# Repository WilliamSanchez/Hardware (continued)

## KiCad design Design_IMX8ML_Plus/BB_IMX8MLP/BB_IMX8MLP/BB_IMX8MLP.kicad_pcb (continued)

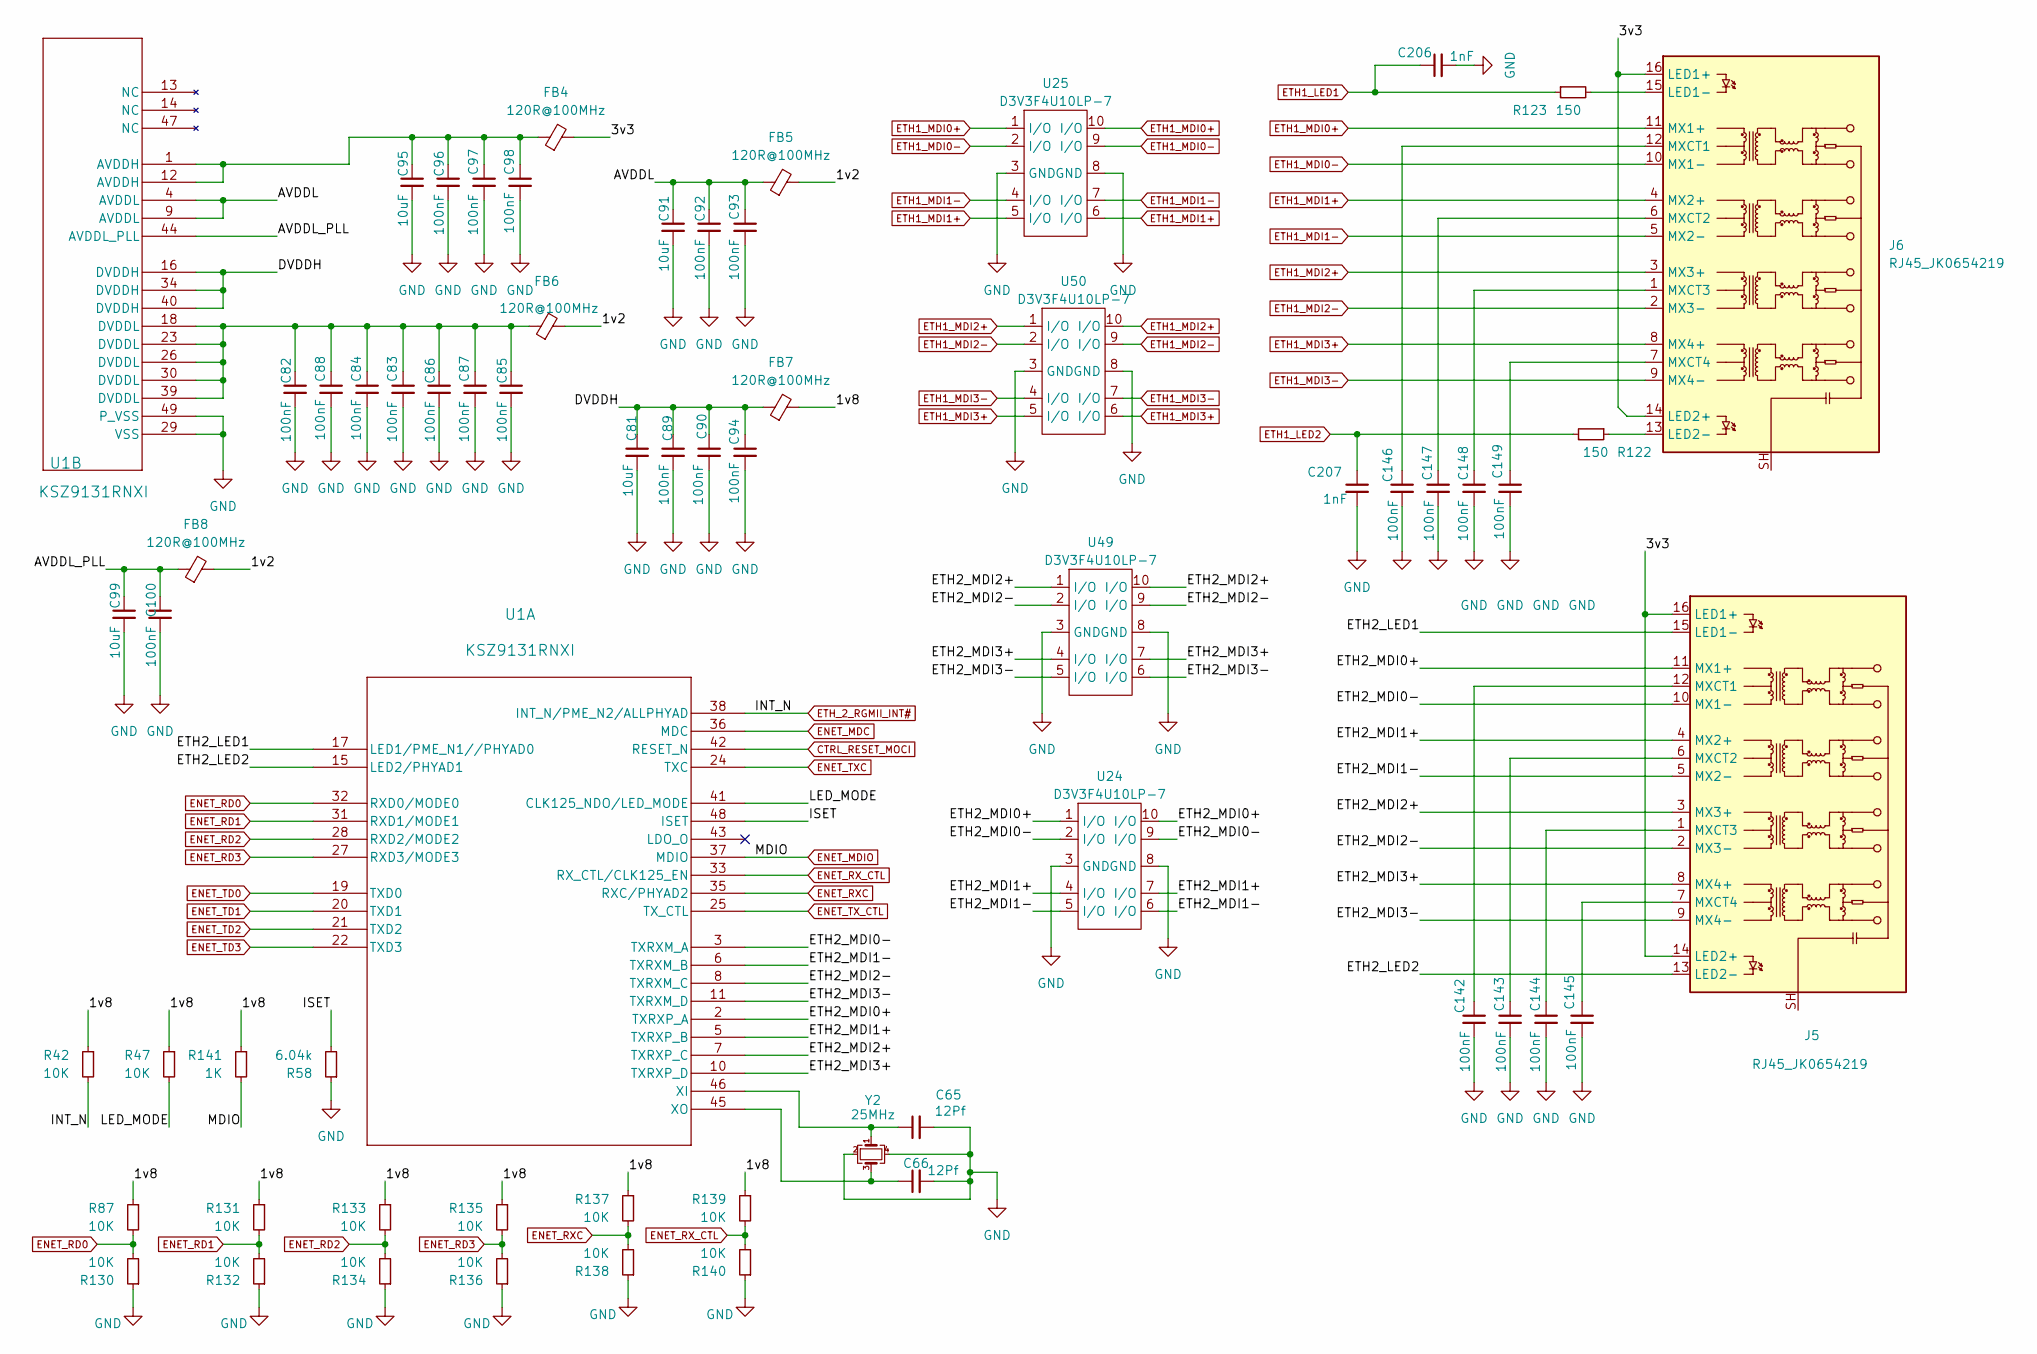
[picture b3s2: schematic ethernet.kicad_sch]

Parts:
C65, C66: 12Pf; C_0402_1005Metric
C81, C91, C95, C99: 10uF; C_0402_1005Metric
C82, C83, C84, C85, C86, C87, C88, C89, C90, C92, C93, C94, C96, C97, C98, C100, C142, C143, C144, C145, C146, C147, C148, C149: 100nF; C_0402_1005Metric
C206, C207: 1nF; C_0402_1005Metric
FB4, FB5, FB6, FB7, FB8: 120R@100MHz; L_0603_1608Metric
J5, J6: RJ45_JK0654219; BEL_A829-1J1T-KM
R42, R47: 10K; R_0402_1005Metric
R58: 6.04k; R_0402_1005Metric
R87, R130, R131, R132, R133, R134, R135, R136, R137, R138, R139, R140: 10K; R_0603_1608Metric
R122, R123: 150; R_0402_1005Metric
R141: 1K; R_0402_1005Metric
U1: KSZ9131RNXI; QFN-48-1EP_7x7mm_P0.5mm_EP5.6x5.6mm
U24, U25, U49, U50: D3V3F4U10LP-7; DFN10_U-DFN2510-10_DIO
Y2: 25MHz; Crystal_SMD_3225-4Pin_3.2x2.5mm

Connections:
/Ethernet/1v2: FB5.2, FB6.2, FB8.2
/Ethernet/1v8: FB7.2, R42.1, R47.1, R87.1, R131.1, R133.1, R135.1, R137.1, R139.1, R141.1
/Ethernet/3v3: FB4.2, J5.14 (LED2+), J5.16 (LED1+), J6.14 (LED2+), J6.16 (LED1+)
/Ethernet/AVDDL: C91.1, C92.1, C93.1, FB5.1, U1.4 (AVDDL), U1.9 (AVDDL)
/Ethernet/AVDDL_PLL: C99.1, C100.1, FB8.1, U1.44 (AVDDL_PLL)
/Ethernet/DVDDH: C81.1, C89.1, C90.1, C94.1, FB7.1, U1.16 (DVDDH), U1.34 (DVDDH), U1.40 (DVDDH)
/Ethernet/ETH2_LED1: J5.15 (LED1-), U1.17 (LED1/PME_N1//PHYAD0)
/Ethernet/ETH2_LED2: J5.13 (LED2-), U1.15 (LED2/PHYAD1)
/Ethernet/ETH2_MDI0+: J5.11 (MX1+), U1.2 (TXRXP_A), U24.1 (I/O), U24.10 (I/O)
/Ethernet/ETH2_MDI0-: J5.10 (MX1-), U1.3 (TXRXM_A), U24.2 (I/O), U24.9 (I/O)
/Ethernet/ETH2_MDI1+: J5.4 (MX2+), U1.5 (TXRXP_B), U24.4 (I/O), U24.7 (I/O)
/Ethernet/ETH2_MDI1-: J5.5 (MX2-), U1.6 (TXRXM_B), U24.5 (I/O), U24.6 (I/O)
/Ethernet/ETH2_MDI2+: J5.3 (MX3+), U1.7 (TXRXP_C), U49.1 (I/O), U49.10 (I/O)
/Ethernet/ETH2_MDI2-: J5.2 (MX3-), U1.8 (TXRXM_C), U49.2 (I/O), U49.9 (I/O)
/Ethernet/ETH2_MDI3+: J5.8 (MX4+), U1.10 (TXRXP_D), U49.4 (I/O), U49.7 (I/O)
/Ethernet/ETH2_MDI3-: J5.9 (MX4-), U1.11 (TXRXM_D), U49.5 (I/O), U49.6 (I/O)
/Ethernet/ISET: R58.2, U1.48 (ISET)
/Ethernet/LED_MODE: R47.2, U1.41 (CLK125_NDO/LED_MODE)
CTRL_RESET_MOCI: U1.42 (RESET_N); also elsewhere on the board
ENET_MDC: U1.36 (MDC); also elsewhere on the board
ENET_MDIO: R141.2, U1.37 (MDIO); also elsewhere on the board
ENET_RD0: R87.2, R130.2, U1.32 (RXD0/MODE0); also elsewhere on the board
ENET_RD1: R131.2, R132.2, U1.31 (RXD1/MODE1); also elsewhere on the board
ENET_RD2: R133.2, R134.2, U1.28 (RXD2/MODE2); also elsewhere on the board
ENET_RD3: R135.2, R136.2, U1.27 (RXD3/MODE3); also elsewhere on the board
ENET_RXC: R137.2, R138.2, U1.35 (RXC/PHYAD2)
ENET_RX_CTL: R139.2, R140.2, U1.33 (RX_CTL/CLK125_EN)
ENET_TD0: U1.19 (TXD0); also elsewhere on the board
ENET_TD1: U1.20 (TXD1); also elsewhere on the board
ENET_TD2: U1.21 (TXD2); also elsewhere on the board
ENET_TD3: U1.22 (TXD3); also elsewhere on the board
ENET_TXC: U1.24 (TXC)
ENET_TX_CTL: U1.25 (TX_CTL)
ETH1_LED1: C206.1, R123.1; also elsewhere on the board
ETH1_LED2: C207.1, R122.2; also elsewhere on the board
ETH1_MDI0+: J6.11 (MX1+), U25.1 (I/O), U25.10 (I/O); also elsewhere on the board
ETH1_MDI0-: J6.10 (MX1-), U25.2 (I/O), U25.9 (I/O); also elsewhere on the board
ETH1_MDI1+: J6.4 (MX2+), U25.5 (I/O), U25.6 (I/O); also elsewhere on the board
ETH1_MDI1-: J6.5 (MX2-), U25.4 (I/O), U25.7 (I/O); also elsewhere on the board
ETH1_MDI2+: J6.3 (MX3+), U50.1 (I/O), U50.10 (I/O); also elsewhere on the board
ETH1_MDI2-: J6.2 (MX3-), U50.2 (I/O), U50.9 (I/O); also elsewhere on the board
ETH1_MDI3+: J6.8 (MX4+), U50.5 (I/O), U50.6 (I/O); also elsewhere on the board
ETH1_MDI3-: J6.9 (MX4-), U50.4 (I/O), U50.7 (I/O); also elsewhere on the board
ETH_2_RGMII_INT#: R42.2, U1.38 (INT_N/PME_N2/ALLPHYAD)
GND: C65.2, C66.2, C81.2, C82.2, C83.2, C84.2, C85.2, C86.2, C87.2, C88.2, C89.2, C90.2, C91.2, C92.2, C93.2, C94.2, C95.2, C96.2, C97.2, C98.2, C99.2, C100.2, C142.2, C143.2, C144.2, C145.2, C146.2, C147.2, C148.2, C149.2, C206.2, C207.2, R58.1, R130.1, R132.1, R134.1, R136.1, R138.1, R140.1, U1.29 (VSS), U1.49 (P_VSS), U24.3 (GND), U24.8 (GND), U25.3 (GND), U25.8 (GND), U49.3 (GND), U49.8 (GND), U50.3 (GND), U50.8 (GND), Y2.2, Y2.4; also elsewhere on the board
unnamed: C82.1, C83.1, C84.1, C85.1, C86.1, C87.1, C88.1, FB6.1, U1.18 (DVDDL), U1.23 (DVDDL), U1.26 (DVDDL), U1.30 (DVDDL), U1.39 (DVDDL)
unnamed: C95.1, C96.1, C97.1, C98.1, FB4.1, U1.1 (AVDDH), U1.12 (AVDDH)
unnamed: C142.1, J5.12 (MXCT1)
unnamed: C143.1, J5.6 (MXCT2)
unnamed: C144.1, J5.1 (MXCT3)
unnamed: C145.1, J5.7 (MXCT4)
unnamed: J6.15 (LED1-), R123.2
unnamed: J6.13 (LED2-), R122.1
unnamed: C146.1, J6.12 (MXCT1)
unnamed: C147.1, J6.6 (MXCT2)
unnamed: C148.1, J6.1 (MXCT3)
unnamed: C149.1, J6.7 (MXCT4)
unnamed: C65.1, U1.46 (XI), Y2.1
unnamed: C66.1, U1.45 (XO), Y2.3

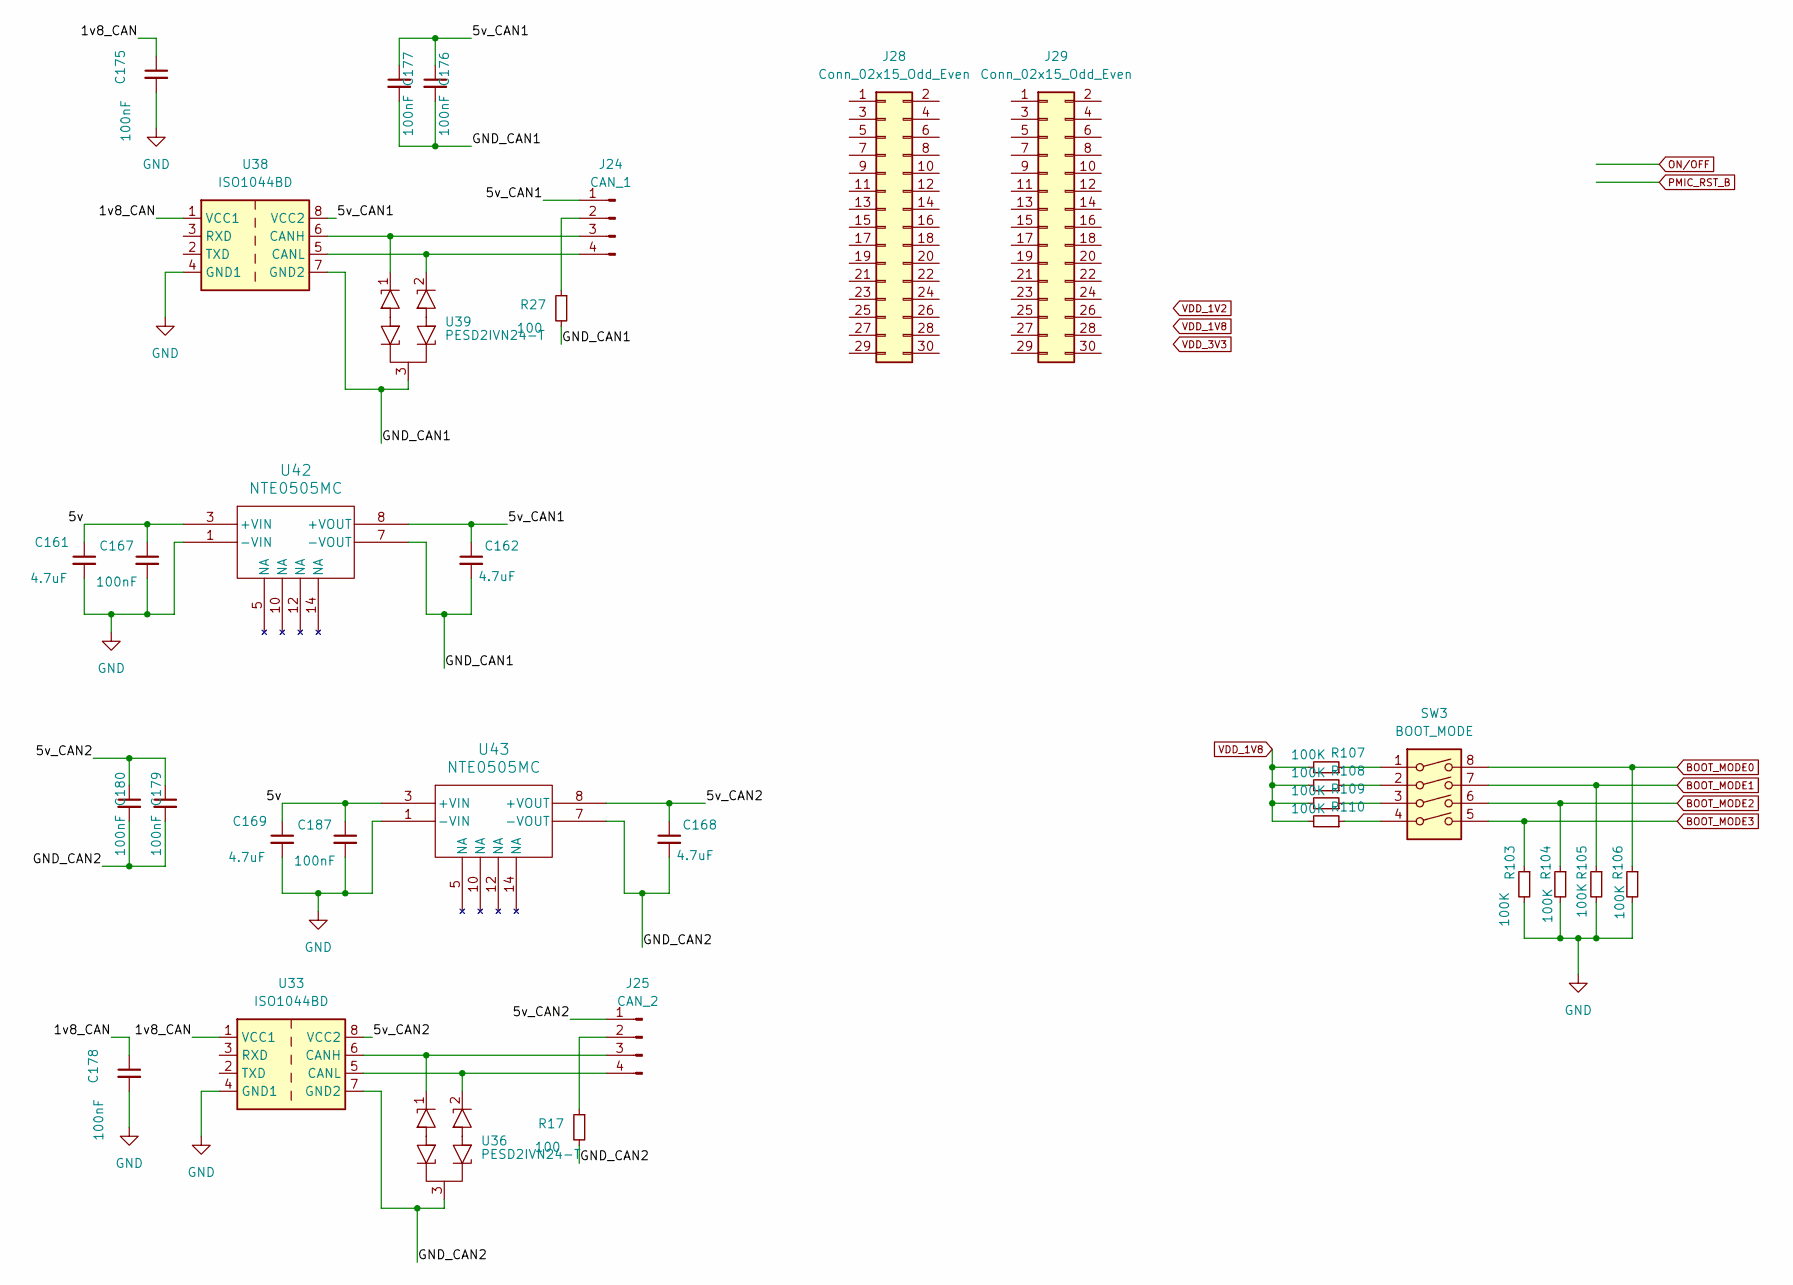
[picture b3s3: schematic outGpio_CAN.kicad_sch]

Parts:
C161, C162, C168, C169: 4.7uF; C_0402_1005Metric
C167, C175, C176, C177, C178, C179, C180, C187: 100nF; C_0402_1005Metric
J24: CAN_1; PinSocket_1x04_P2.54mm_Vertical
J25: CAN_2; PinSocket_1x04_P2.54mm_Vertical
J28, J29: Conn_02x15_Odd_Even; PinHeader_2x16_P2.54mm_Vertical
R17, R27: 100; R_0402_1005Metric
R103, R104, R105, R106, R107, R108, R109, R110: 100K; R_0402_1005Metric
SW3: BOOT_MODE; SW_DIP_SPSTx04_Slide_9.78x12.34mm_W7.62mm_P2.54mm
U33, U38: ISO1044BD; SOIC-8_3.9x4.9mm_P1.27mm
U36, U39: PESD2IVN24-T; SOT-23-3
U42, U43: NTE0505MC; NTE_SINGLE_M_MUR

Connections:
/OutGPIO_CAN/1v8_CAN: C175.1, C178.1, U33.1 (VCC1), U38.1 (VCC1)
/OutGPIO_CAN/5v: C161.1, C167.1, C169.1, C187.1, U42.3 (+VIN), U43.3 (+VIN)
/OutGPIO_CAN/5v_CAN1: C162.1, C176.1, C177.1, J24.1, U38.8 (VCC2), U42.8 (+VOUT)
/OutGPIO_CAN/5v_CAN2: C168.1, C179.1, C180.1, J25.1, U33.8 (VCC2), U43.8 (+VOUT)
/OutGPIO_CAN/GND_CAN1: C162.2, C176.2, C177.2, R27.2, U38.7 (GND2), U39.3, U42.7 (-VOUT)
/OutGPIO_CAN/GND_CAN2: C168.2, C179.2, C180.2, R17.2, U33.7 (GND2), U36.3, U43.7 (-VOUT)
BOOT_MODE0: R106.1, SW3.8; also elsewhere on the board
BOOT_MODE1: R105.1, SW3.7; also elsewhere on the board
BOOT_MODE2: R104.1, SW3.6; also elsewhere on the board
BOOT_MODE3: R103.1, SW3.5; also elsewhere on the board
GND: C161.2, C167.2, C169.2, C175.2, C178.2, C187.2, R103.2, R104.2, R105.2, R106.2, U33.4 (GND1), U38.4 (GND1), U42.1 (-VIN), U43.1 (-VIN); also elsewhere on the board
unnamed: J24.2, R27.1
unnamed: J24.3, U38.6 (CANH), U39.1
unnamed: J24.4, U38.5 (CANL), U39.2
unnamed: J25.2, R17.1
unnamed: J25.3, U33.6 (CANH), U36.1
unnamed: J25.4, U33.5 (CANL), U36.2
unnamed: R107.1, SW3.1
unnamed: R108.1, SW3.2
unnamed: R109.1, SW3.3
unnamed: R110.1, SW3.4
VDD_1V8: R107.2, R108.2, R109.2, R110.2; also elsewhere on the board

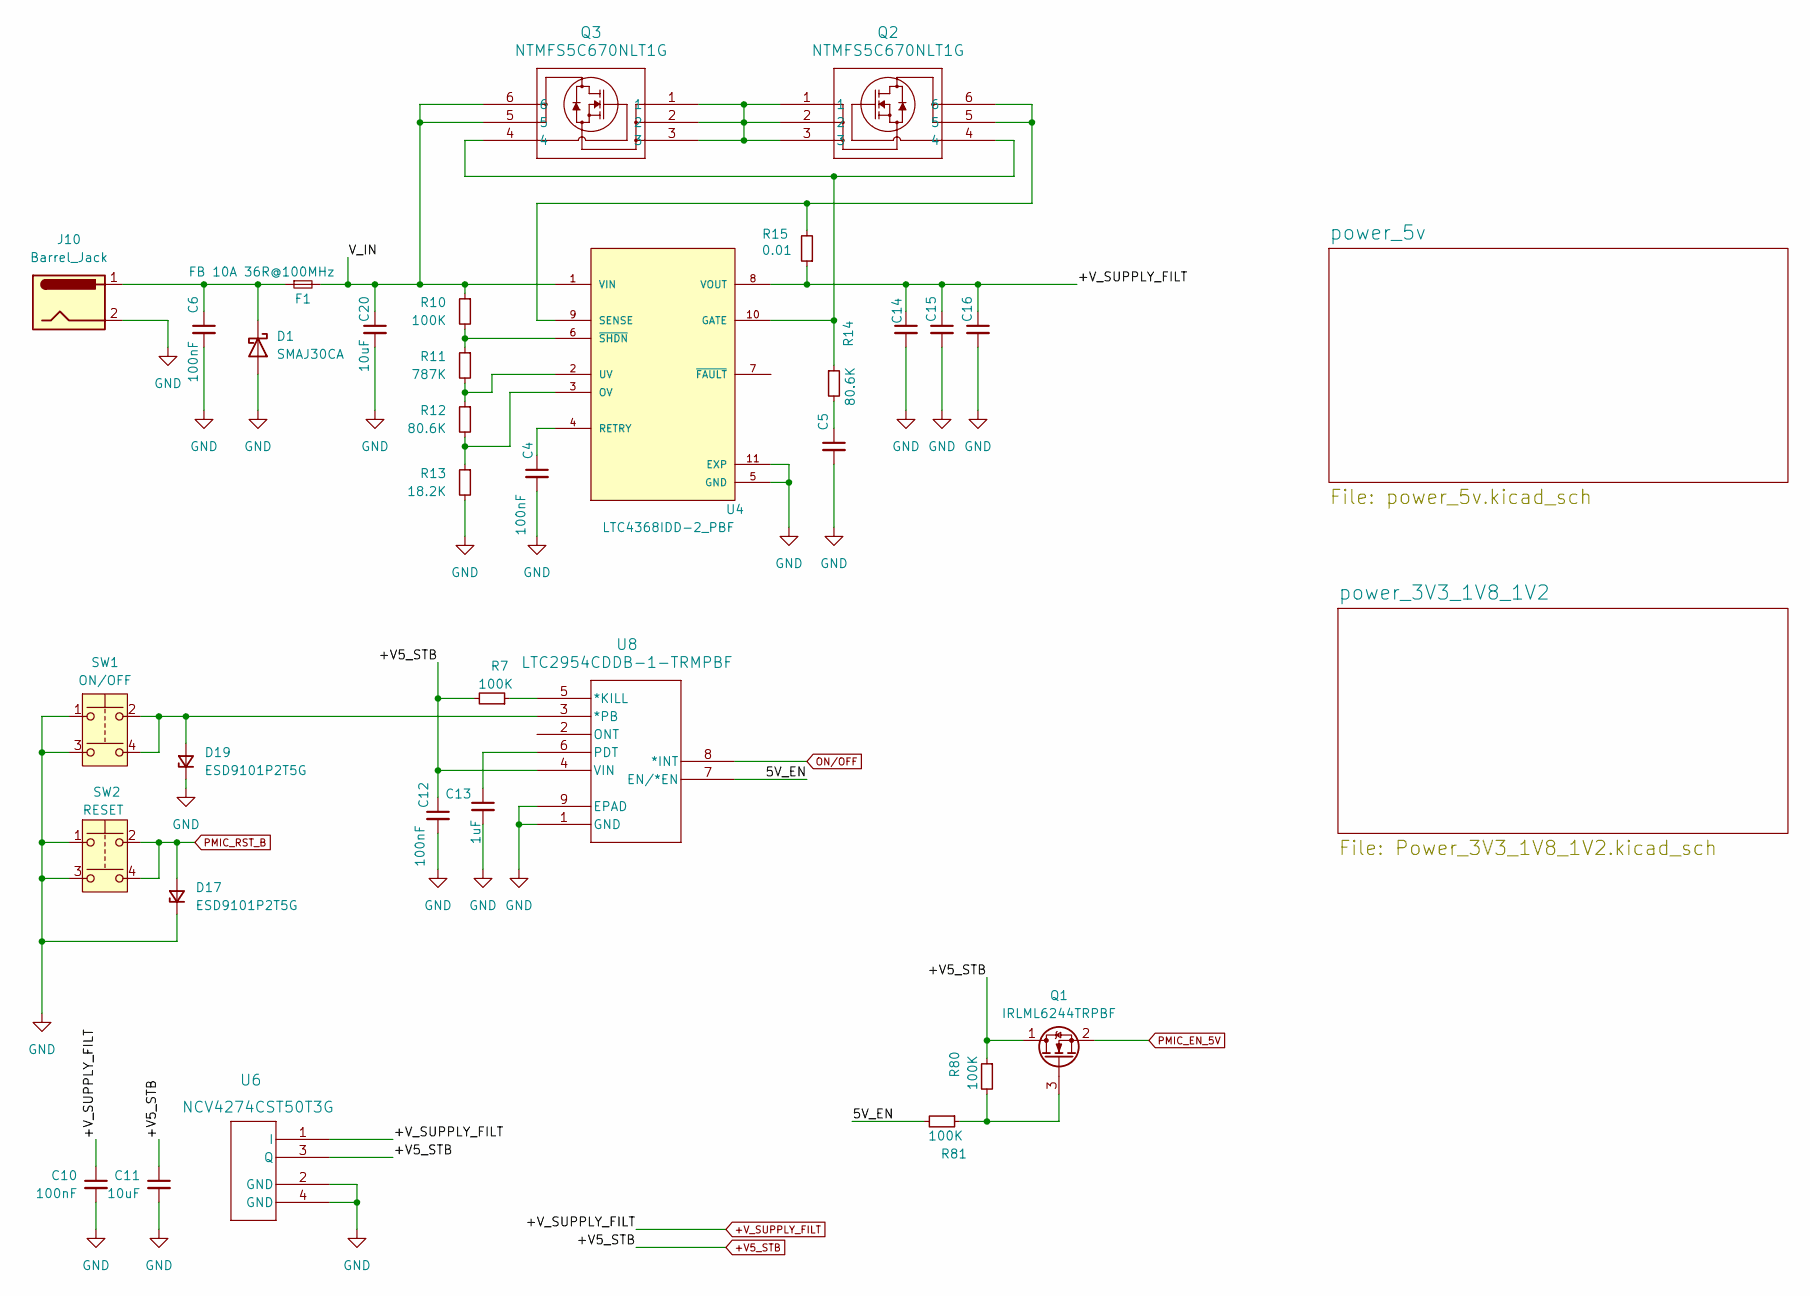
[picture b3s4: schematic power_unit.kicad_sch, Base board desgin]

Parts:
C4, C6, C10, C12: 100nF; C_0402_1005Metric
C5: 2.2nF; C_0805_2012Metric
C11: 10uF; C_0402_1005Metric
C13: 1uF; C_0402_1005Metric
C14, C15, C16, C20: 10uF; C_1210_3225Metric
D1: SMAJ30CA; D_SMA
D17, D19: ESD9101P2T5G; D_SOD-923
F1: FB 10A 36R@100MHz; FB_35F0121-0SR-10
J10: Barrel_Jack; BarrelJack_CUI_PJ-063AH_Horizontal
Q1: IRLML6244TRPBF; SOT-23-3
Q2, Q3: NTMFS5C670NLT1G; NTMFS5C670NLT1G_ONS
R7, R10, R80, R81: 100K; R_0402_1005Metric
R11: 787K; R_0402_1005Metric
R12, R14: 80.6K; R_0402_1005Metric
R13: 18.2K; R_0402_1005Metric
R15: 0.01; R_1206_3216Metric
SW1: ON/OFF; SW_SPST_TL3342
SW2: RESET; SW_SPST_TL3342
U4: LTC4368IDD-2_PBF; SON50P300X300X80-11N; PARTREV A
U6: NCV4274CST50T3G; SOT-223_ONS
U8: LTC2954CDDB-1-TRMPBF; DFN-8_DDB_LIT

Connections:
+V5_STB: C11.1, C12.1, Q1.1 (D), R7.2, R80.1, U6.3 (Q), U8.4 (VIN); also elsewhere on the board
+V_SUPPLY_FILT: C10.1, C14.1, C15.1, C16.1, R15.1, U4.8 (VOUT), U6.1 (I); also elsewhere on the board
/power_unit/5V_EN: R81.2, U8.7 (EN/*EN)
/power_unit/V_IN: C20.1, F1.2, Q3.5, Q3.6, R10.1, U4.1 (VIN)
GND: C4.2, C5.2, C6.2, C10.2, C11.2, C12.2, C13.2, C14.2, C15.2, C16.2, C20.2, D1.2 (A), D17.1 (K), D19.1 (K), J10.2, R13.2, SW1.1, SW1.3, SW2.1, SW2.3, U4.5 (GND), U4.11 (EXP), U6.2 (GND), U6.4 (GND), U8.1 (GND), U8.9 (EPAD); also elsewhere on the board
unnamed: C5.1, R14.2
unnamed: C6.1, D1.1 (K), F1.1, J10.1
unnamed: D19.2 (A), SW1.2, SW1.4, U8.3 (*PB)
unnamed: Q1.3 (G), R80.2, R81.1
unnamed: Q2.1, Q2.2, Q2.3, Q3.1, Q3.2, Q3.3
unnamed: Q2.4, Q3.4, R14.1, U4.10 (GATE)
unnamed: R12.2, R13.1, U4.3 (OV)
unnamed: C4.1, U4.4 (RETRY)
unnamed: Q2.5, Q2.6, R15.2, U4.9 (SENSE)
unnamed: R11.2, R12.1, U4.2 (UV)
unnamed: R10.2, R11.1, U4.6 (~SHDN)
unnamed: R7.1, U8.5 (*KILL)
unnamed: C13.1, U8.6 (PDT)
ON/OFF: U8.8 (*INT); also elsewhere on the board
PMIC_EN_5V: Q1.2 (S); also elsewhere on the board
PMIC_RST_B: D17.2 (A), SW2.2, SW2.4; also elsewhere on the board

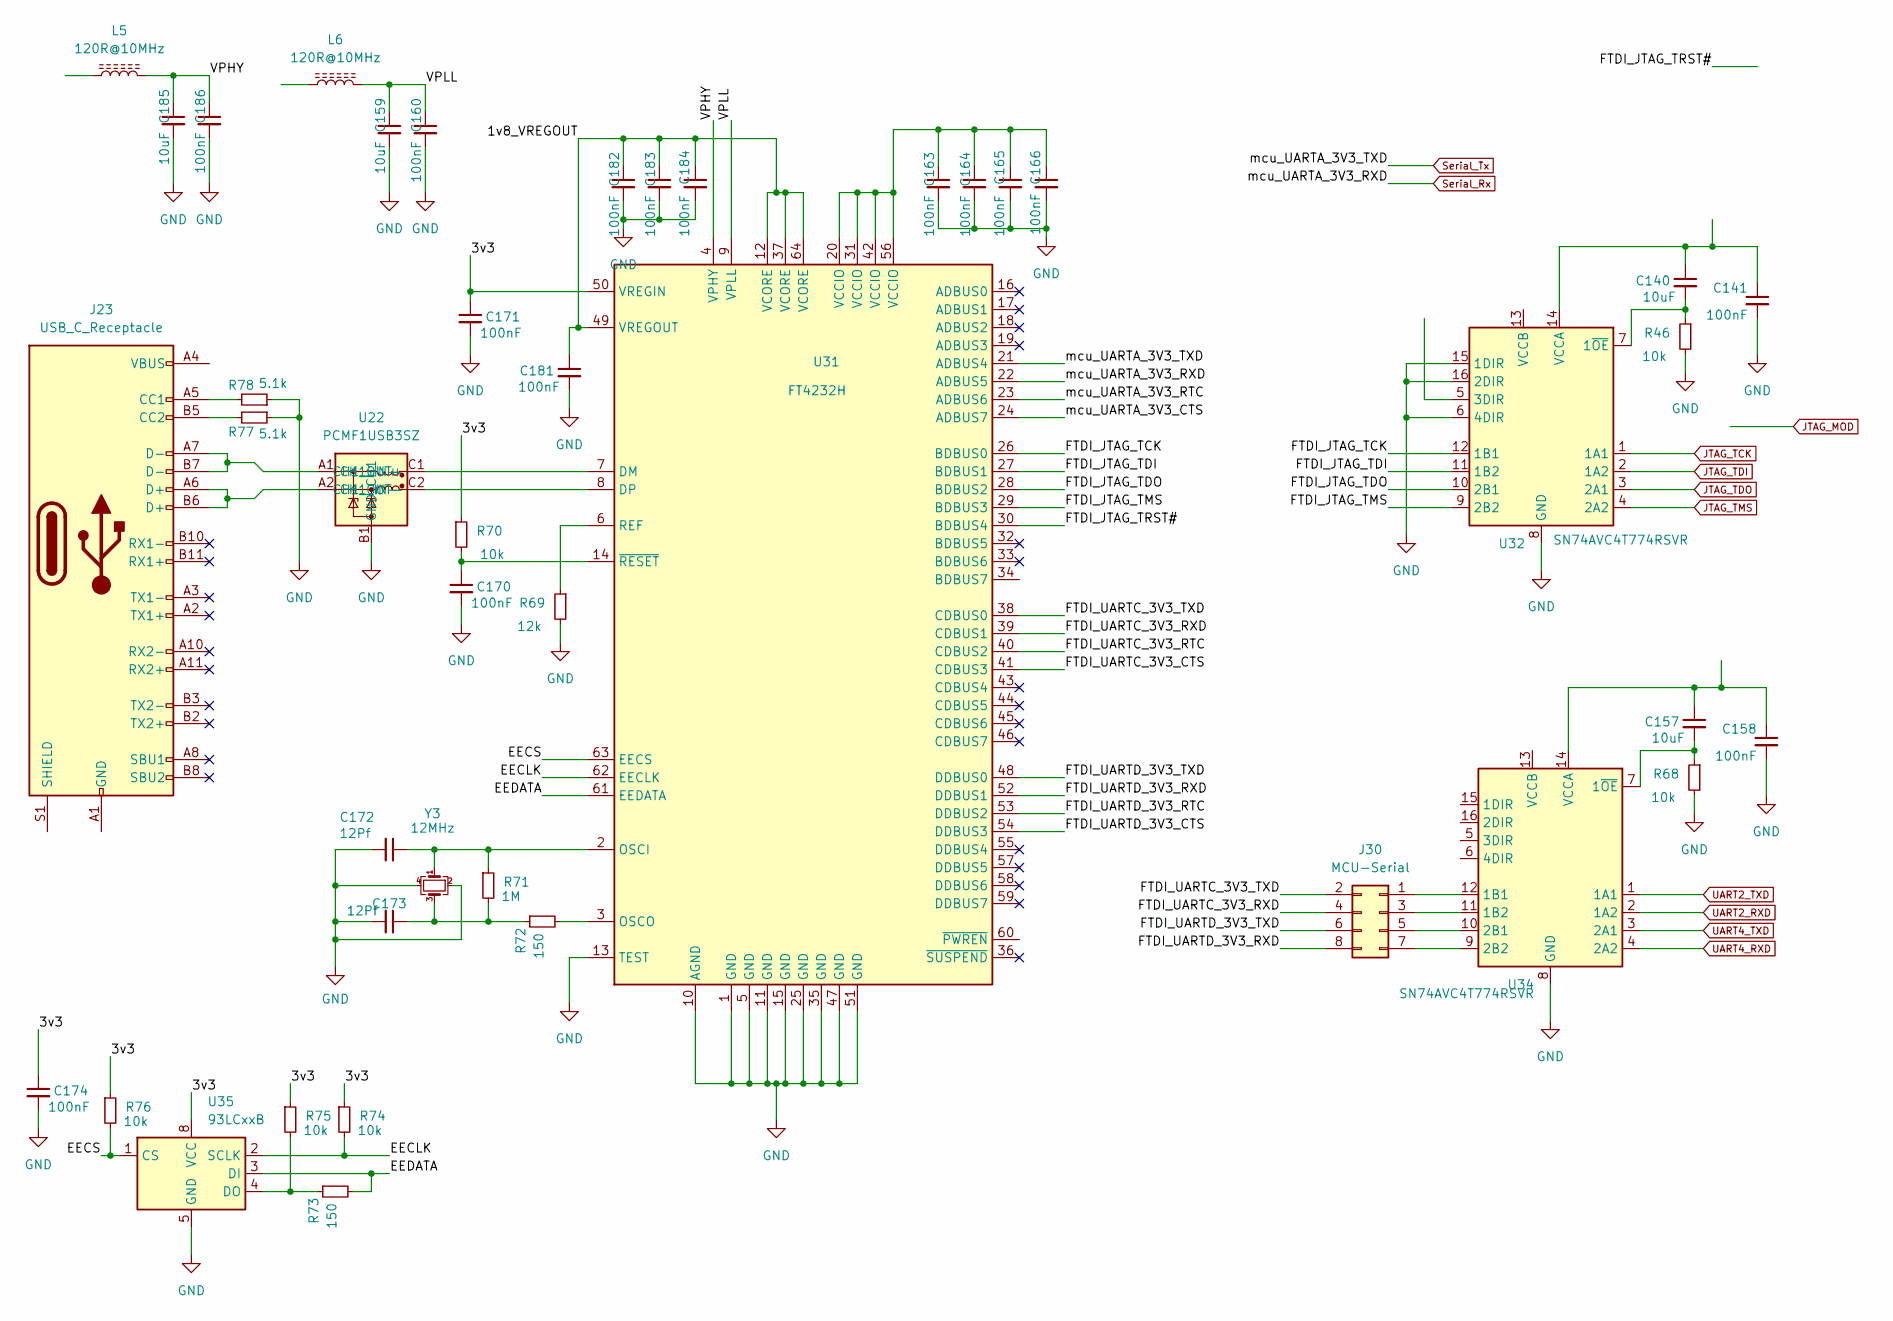
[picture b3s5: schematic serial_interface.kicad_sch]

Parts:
C140, C157, C159, C185: 10uF; C_0402_1005Metric
C141, C158, C160, C163, C164, C165, C166, C170, C171, C174, C181, C182, C183, C184, C186: 100nF; C_0402_1005Metric
C172, C173: 12Pf; C_0402_1005Metric
J23: USB_C_Receptacle; USB_C_Receptacle_GCT_USB4110
J30: MCU-Serial; PinHeader_2x04_P2.54mm_Vertical
L5, L6: 120R@10MHz; FIL_EXC-14CH120U
R46, R68, R70, R74, R75, R76: 10k; R_0402_1005Metric
R69: 12k; R_0402_1005Metric
R71: 1M; R_0402_1005Metric
R72, R73: 150; R_0402_1005Metric
R77, R78: 5.1k; R_0402_1005Metric
U22: PCMF1USB3SZ; BGA5N35P3X2_109X74X40N
U31: FT4232H; VQFN-64-1EP_9x9mm_P0.5mm_EP5.4x5.4mm
U32, U34: SN74AVC4T774RSVR; UQFN-16_1.8x2.6mm_P0.4mm
U35: 93LCxxB; DFN-8-1EP_3x2mm_P0.5mm_EP1.7x1.4mm
Y3: 12MHz; Crystal_SMD_3225-4Pin_3.2x2.5mm

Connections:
/serial_interface/1v8_VREGOUT: C181.1, C182.1, C183.1, C184.1, U31.12 (VCORE), U31.37 (VCORE), U31.49 (VREGOUT), U31.64 (VCORE)
/serial_interface/3v3: C171.1, C174.1, R70.1, R74.1, R75.1, R76.1, U31.50 (VREGIN), U35.8 (VCC)
/serial_interface/EECLK: R74.2, U31.62 (EECLK), U35.2 (SCLK)
/serial_interface/EECS: R76.2, U31.63 (EECS), U35.1 (CS)
/serial_interface/EEDATA: R73.2, U31.61 (EEDATA), U35.3 (DI)
/serial_interface/FTDI_JTAG_TCK: U31.26 (BDBUS0), U32.12 (1B1)
/serial_interface/FTDI_JTAG_TDI: U31.27 (BDBUS1), U32.11 (1B2)
/serial_interface/FTDI_JTAG_TDO: U31.28 (BDBUS2), U32.10 (2B1)
/serial_interface/FTDI_JTAG_TMS: U31.29 (BDBUS3), U32.9 (2B2)
/serial_interface/FTDI_JTAG_TRST#: U31.30 (BDBUS4)
/serial_interface/FTDI_UARTC_3V3_CTS: U31.41 (CDBUS3)
/serial_interface/FTDI_UARTC_3V3_RTC: U31.40 (CDBUS2)
/serial_interface/FTDI_UARTC_3V3_RXD: J30.4, U31.39 (CDBUS1)
/serial_interface/FTDI_UARTC_3V3_TXD: J30.2, U31.38 (CDBUS0)
/serial_interface/FTDI_UARTD_3V3_CTS: U31.54 (DDBUS3)
/serial_interface/FTDI_UARTD_3V3_RTC: U31.53 (DDBUS2)
/serial_interface/FTDI_UARTD_3V3_RXD: J30.8, U31.52 (DDBUS1)
/serial_interface/FTDI_UARTD_3V3_TXD: J30.6, U31.48 (DDBUS0)
/serial_interface/VPHY: C185.1, C186.1, L5.2 (2_2), U31.4 (VPHY)
/serial_interface/VPLL: C159.1, C160.1, L6.2 (2_2), U31.9 (VPLL)
/serial_interface/mcu_UARTA_3V3_CTS: U31.24 (ADBUS7)
/serial_interface/mcu_UARTA_3V3_RTC: U31.23 (ADBUS6)
GND: C141.2, C158.2, C159.2, C160.2, C163.2, C164.2, C165.2, C166.2, C170.2, C171.2, C172.2, C173.2, C174.2, C181.2, C182.2, C183.2, C184.2, C185.2, C186.2, R46.2, R68.2, R69.2, R77.1, R78.1, U22.B1 (GND_CH1), U31.1 (GND), U31.5 (GND), U31.10 (AGND), U31.11 (GND), U31.13 (TEST), U31.15 (GND), U31.25 (GND), U31.35 (GND), U31.47 (GND), U31.51 (GND), U32.6 (4DIR), U32.8 (GND), U32.15 (1DIR), U32.16 (2DIR), U34.8 (GND), U35.5 (GND), Y3.2, Y3.4; also elsewhere on the board
JTAG_TCK: U32.1 (1A1); also elsewhere on the board
JTAG_TDI: U32.2 (1A2); also elsewhere on the board
JTAG_TDO: U32.3 (2A1); also elsewhere on the board
JTAG_TMS: U32.4 (2A2); also elsewhere on the board
unnamed: C163.1, C164.1, C165.1, C166.1, U31.20 (VCCIO), U31.31 (VCCIO), U31.42 (VCCIO), U31.56 (VCCIO)
unnamed: C173.1, R71.2, R72.1, Y3.3
unnamed: J23.A5 (CC1), R78.2
unnamed: J23.B5 (CC2), R77.2
unnamed: J23.A1 (GND), J23.A12 (GND), J23.B1 (GND), J23.B12 (GND)
unnamed: J23.A4 (VBUS), J23.A9 (VBUS), J23.B4 (VBUS), J23.B9 (VBUS)
unnamed: J30.1, U34.12 (1B1)
unnamed: J30.3, U34.11 (1B2)
unnamed: J30.5, U34.10 (2B1)
unnamed: J30.7, U34.9 (2B2)
unnamed: J23.A7 (D-), J23.B7 (D-), U22.A1 (CH1_IN+)
unnamed: J23.A6 (D+), J23.B6 (D+), U22.A2 (CH1_IN-)
unnamed: U22.C1 (CH1_OUT+), U31.7 (DM)
unnamed: U22.C2 (CH1_OUT-), U31.8 (DP)
unnamed: C172.1, R71.1, U31.2 (OSCI), Y3.1
unnamed: R72.2, U31.3 (OSCO)
unnamed: R69.1, U31.6 (REF)
unnamed: C170.1, R70.2, U31.14 (~RESET)
unnamed: C140.2, R46.1, U32.7 (1~OE)
unnamed: C140.1, C141.1, U32.14 (VCCA)
unnamed: C157.2, R68.1, U34.7 (1~OE)
unnamed: C157.1, C158.1, U34.14 (VCCA)
unnamed: R73.1, R75.2, U35.4 (DO)
Serial_Rx: U31.22 (ADBUS5); also elsewhere on the board
Serial_Tx: U31.21 (ADBUS4); also elsewhere on the board
UART2_RXD: U34.2 (1A2); also elsewhere on the board
UART2_TXD: U34.1 (1A1); also elsewhere on the board
UART4_RXD: U34.4 (2A2); also elsewhere on the board
UART4_TXD: U34.3 (2A1); also elsewhere on the board

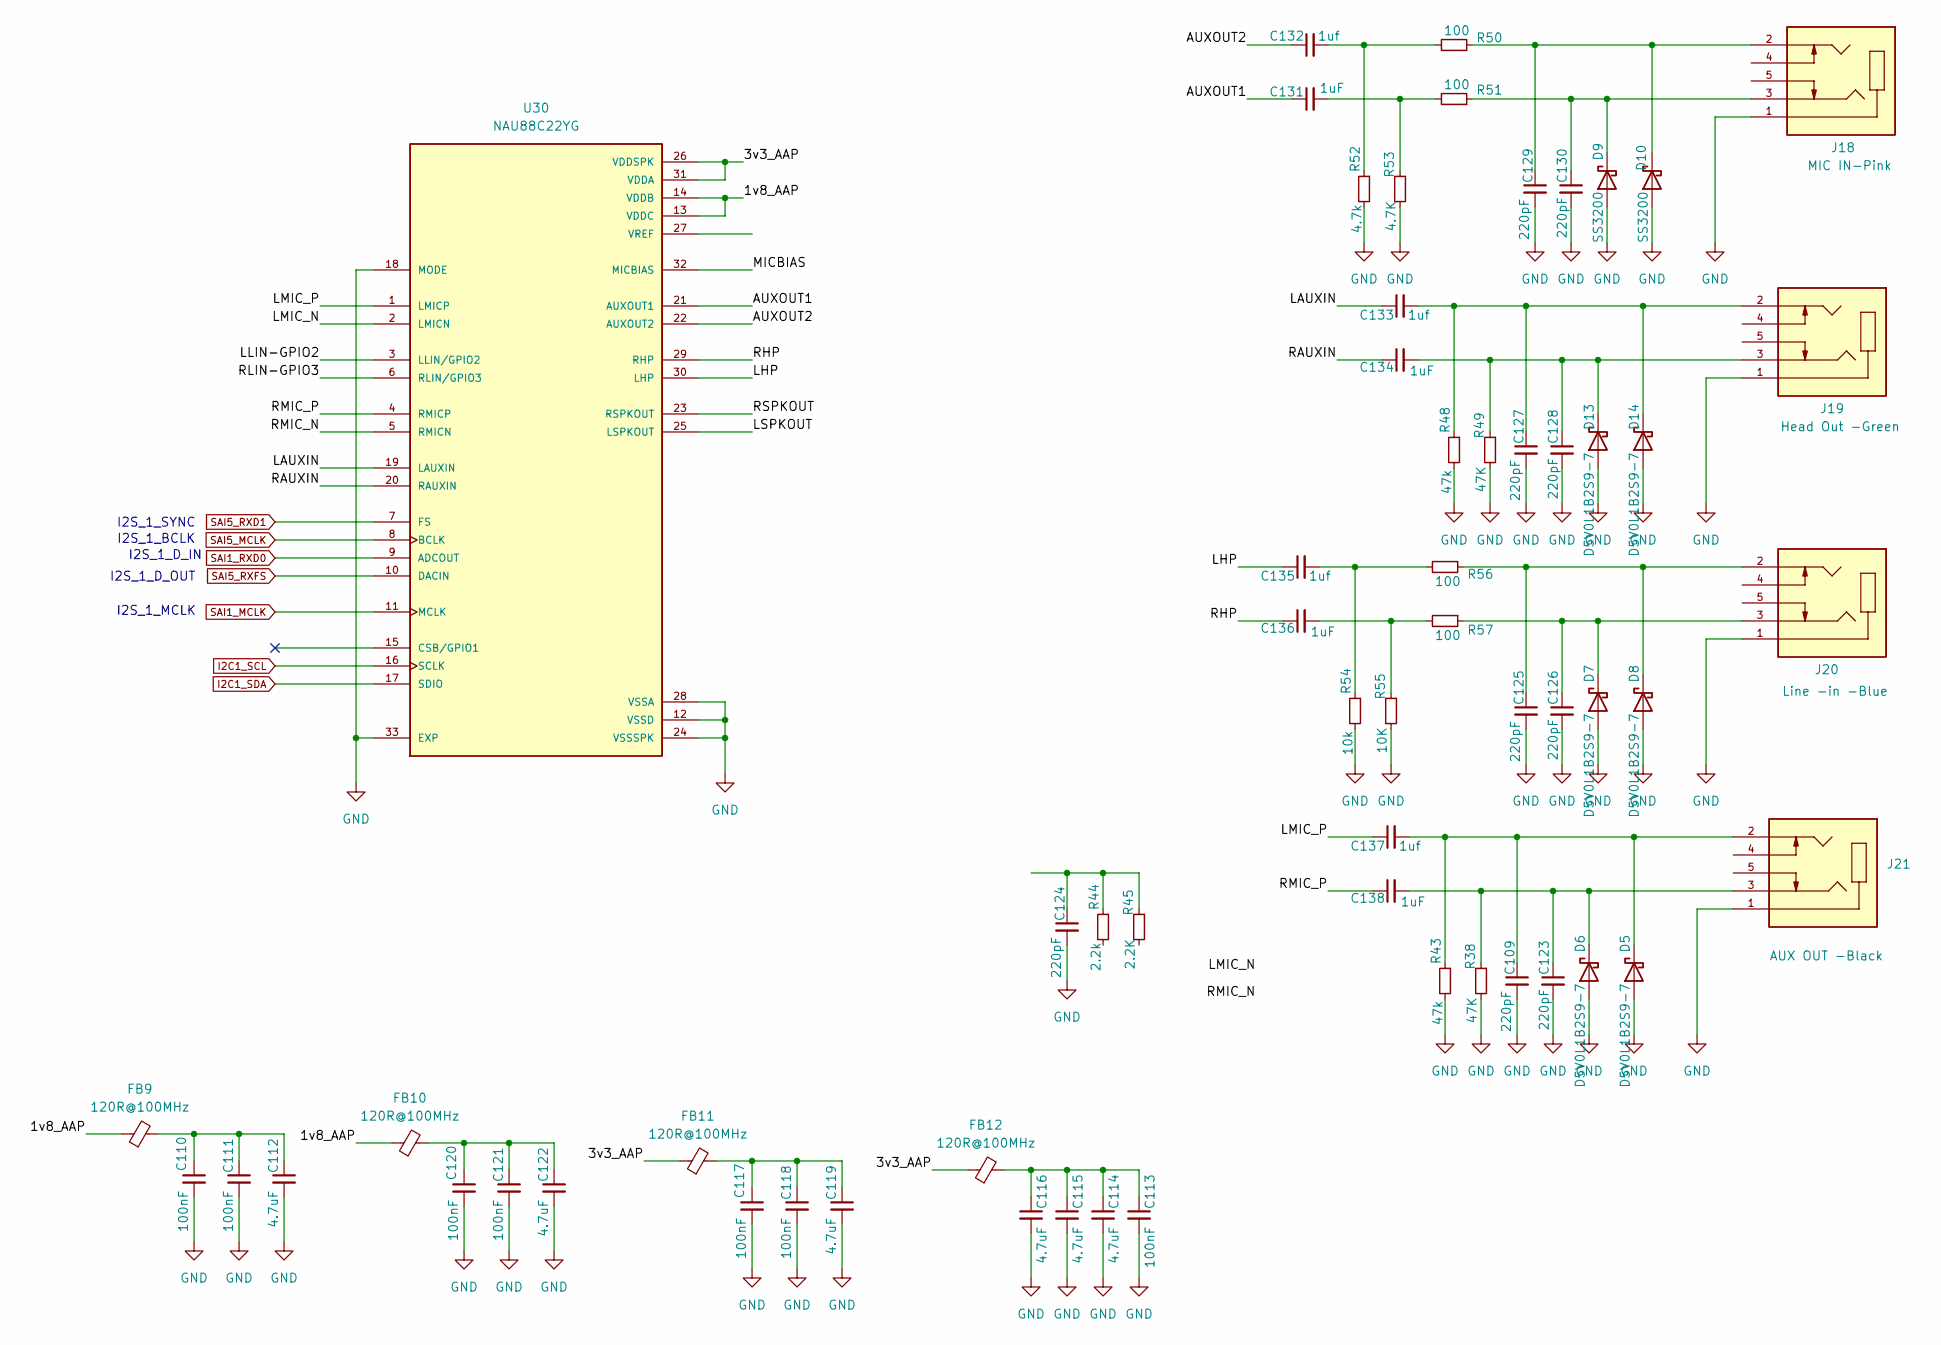
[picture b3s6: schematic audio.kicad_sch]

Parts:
C109, C123, C124, C125, C126, C127, C128, C129, C130: 220pF; C_0402_1005Metric
C110, C111, C113, C117, C118, C120, C121: 100nF; C_0402_1005Metric
C112, C114, C115, C116, C119, C122: 4.7uF; C_0402_1005Metric
C131, C134, C136, C138: 1uF; C_0402_1005Metric
C132, C133, C135, C137: 1uf; C_0402_1005Metric
D5, D6, D7, D8, D13, D14: D5V0L1B2S9-7; D_SOD-923
D9, D10: SS3200; D_SOD-923
FB9, FB10, FB11, FB12: 120R@100MHz; L_0603_1608Metric
J18: MIC IN-Pink; CUI_SJ1-3535NG-PI; PARTREV 1.02
J19: Head Out -Green; CUI_SJ1-3535NG-PI; PARTREV 1.02
J20: Line -in -Blue; CUI_SJ1-3535NG-PI; PARTREV 1.02
J21: AUX OUT -Black; CUI_SJ1-3535NG-PI; PARTREV 1.02
R38, R49: 47K; R_0402_1005Metric
R43, R48: 47k; R_0402_1005Metric
R44: 2.2k; R_0402_1005Metric
R45: 2.2K; R_0402_1005Metric
R50, R51, R56, R57: 100; R_0402_1005Metric
R52: 4.7k; R_0402_1005Metric
R53: 4.7K; R_0402_1005Metric
R54: 10k; R_0402_1005Metric
R55: 10K; R_0402_1005Metric
U30: NAU88C22YG; QFN50P500X500X80-33N; PARTREV 3.3

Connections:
/Audio/1v8_AAP: FB9.1, FB10.1, U30.13 (VDDC), U30.14 (VDDB)
/Audio/3v3_AAP: FB11.1, FB12.1, U30.26 (VDDSPK), U30.31 (VDDA)
/Audio/AUXOUT1: C131.1, U30.21 (AUXOUT1)
/Audio/AUXOUT2: C132.1, U30.22 (AUXOUT2)
/Audio/LAUXIN: C133.1, U30.19 (LAUXIN)
/Audio/LHP: C135.1, U30.30 (LHP)
/Audio/LLIN-GPIO2: U30.3 (LLIN/GPIO2)
/Audio/LMIC_N: U30.2 (LMICN)
/Audio/LMIC_P: C137.1, U30.1 (LMICP)
/Audio/LSPKOUT: U30.25 (LSPKOUT)
/Audio/MICBIAS: U30.32 (MICBIAS)
/Audio/RAUXIN: C134.1, U30.20 (RAUXIN)
/Audio/RHP: C136.1, U30.29 (RHP)
/Audio/RLIN-GPIO3: U30.6 (RLIN/GPIO3)
/Audio/RMIC_N: U30.5 (RMICN)
/Audio/RMIC_P: C138.1, U30.4 (RMICP)
/Audio/RSPKOUT: U30.23 (RSPKOUT)
GND: C109.2, C110.2, C111.2, C112.2, C113.2, C114.2, C115.2, C116.2, C117.2, C118.2, C119.2, C120.2, C121.2, C122.2, C123.2, C124.2, C125.2, C126.2, C127.2, C128.2, C129.2, C130.2, D5.2 (A), D6.2 (A), D7.2 (A), D8.2 (A), D9.2 (A), D10.2 (A), D13.2 (A), D14.2 (A), J18.1, J19.1, J20.1, J21.1, R38.2, R43.2, R48.2, R49.2, R52.2, R53.2, R54.2, R55.2, U30.12 (VSSD), U30.18 (MODE), U30.24 (VSSSPK), U30.28 (VSSA), U30.33 (EXP); also elsewhere on the board
I2C1_SCL: U30.16 (SCLK); also elsewhere on the board
I2C1_SDA: U30.17 (SDIO); also elsewhere on the board
unnamed: C110.1, C111.1, C112.1, FB9.2
unnamed: C113.1, C114.1, C115.1, C116.1, FB12.2
unnamed: C117.1, C118.1, C119.1, FB11.2
unnamed: C120.1, C121.1, C122.1, FB10.2
unnamed: C124.1, R44.1, R45.1
unnamed: C131.2, R51.2, R53.1
unnamed: C132.2, R50.2, R52.1
unnamed: C135.2, R54.1, R56.2
unnamed: C136.2, R55.1, R57.2
unnamed: C109.1, C137.2, D5.1 (K), J21.2, R43.1
unnamed: C123.1, C138.2, D6.1 (K), J21.3, R38.1
unnamed: C126.1, D7.1 (K), J20.3, R57.1
unnamed: C125.1, D8.1 (K), J20.2, R56.1
unnamed: C130.1, D9.1 (K), J18.3, R51.1
unnamed: C129.1, D10.1 (K), J18.2, R50.1
unnamed: C128.1, C134.2, D13.1 (K), J19.3, R49.1
unnamed: C127.1, C133.2, D14.1 (K), J19.2, R48.1
SAI1_MCLK: U30.11 (MCLK); also elsewhere on the board
SAI1_RXD0: U30.9 (ADCOUT); also elsewhere on the board
SAI5_MCLK: U30.8 (BCLK); also elsewhere on the board
SAI5_RXD1: U30.7 (FS); also elsewhere on the board
SAI5_RXFS: U30.10 (DACIN); also elsewhere on the board

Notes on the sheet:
I2S_1_D_OUT
I2S_1_MCLK
I2S_1_SYNC
I2S_1_D_IN
I2S_1_BCLK
